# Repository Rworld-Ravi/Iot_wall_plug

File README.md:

# IoT wall plug standard

This is a circuit to control any 220v AC device under 4A plugged it.  

## Getting Started with another firmware  

To program the ESP8266 ESP-07 you need an USB <--> serial converter at 3,3v (5v will damage the ESP-07 IOs).  
You can use Arduino IDE to update own sketches.  
Or you can install another firmware in ESP-07 as Lua, uPython, ESPeasy...  
To install another firmware:
* Disconnect device from power  
* Shortcut jumper (IO0 and GND)  
* Connect your favorite USB-serial converter at RX,TX,GND pins  
* Apply power to device (Be careful with 220v AC)
* Upload your firmware with esptool.exe (windows) or another tool for OSX, Linux...  
* Disconnect the jumper (IO0 and GND)
* And restart device

## Built With

[EagleCAD](https://www.autodesk.com/products/eagle/overview)

## Authors

* **RadikalBytes** - *Alfredo Prado* - [@radikalbytes](https://twitter.com/radikalbytes)

## License
<br />This work is licensed under a <a rel="license" href="http://creativecommons.org/licenses/by-sa/3.0/">Creative Commons Attribution-ShareAlike 3.0 Unported License</a>.

## Acknowledgments

* To my brain for support me every hour ;)

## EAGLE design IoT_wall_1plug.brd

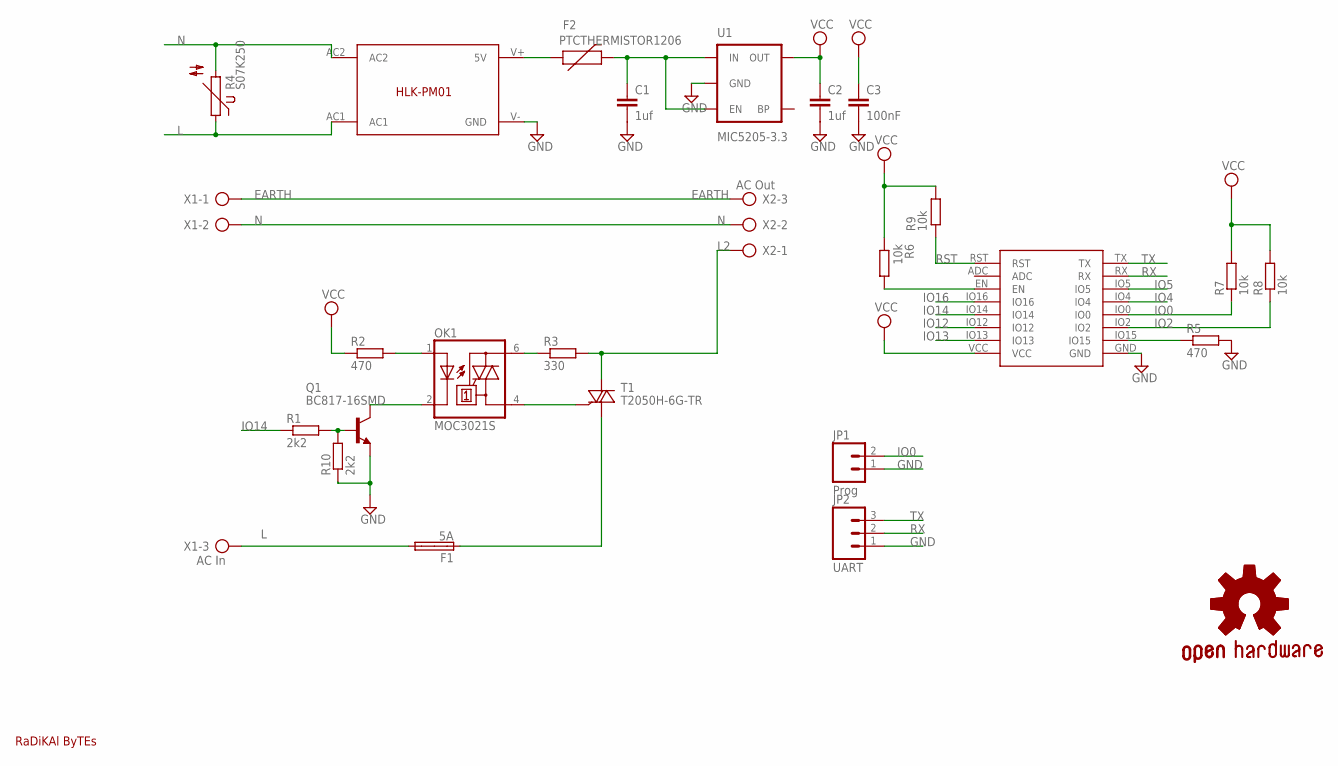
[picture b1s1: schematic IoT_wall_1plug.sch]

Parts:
C1, C2: 1uf; RCL_C0805K
C3: 100nF; RCL_C0805K
F1: 5A; SHK20Q
F2: PTCTHERMISTOR1206; SPARKFUN-POWERIC_PTC-1206
GOLD_ORB_SM1: OSHWLOGO_GOLD_ORB_MED; OSHW1
JP1: Prog; SPARKFUN-CONNECTORS_1X02
JP2: UART; SPARKFUN-CONNECTORS_1X03
OK1: MOC3021S; DIL6-SMD
Q1: BC817-16SMD; SOT23-BEC
R1, R10: 2k2; R0805
R2, R5: 470; R0805
R3: 330; R0805
R4: S07K250
R6, R7, R8, R9: 10k; R0805
T1: T2050H-6G-TR; D2PAK-3
U1: MIC5205-3.3; SPARKFUN-POWERIC_SOT23-5
U$1: HLK-PM01
U$2: DAVLIB_ESP8266
U$4: MI_LOGO1.5MM; MI_LOGO_PEQUEÑO
X1: AC In; AK500/3
X2: AC Out; AK500/3

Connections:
EARTH: X1.1, X2.3
GND: C1.2, C2.2, C3.2, JP1.1, JP2.1, Q1.E, R5.2, R10.1, U1.2 (GND), U$1.V- (GND), U$2.GND
IO0: JP1.2, R7.1, U$2.IO0
IO2: R8.1, U$2.IO2
IO4: U$2.IO4
IO5: U$2.IO5
IO12: U$2.IO12
IO13: U$2.IO13
IO14: R1.1, U$2.IO14
IO16: U$2.IO16
L: F1.2A, R4.1, U$1.AC1, X1.3
L2: R3.2, T1.4 (A2), X2.1
N: R4.2, U$1.AC2, X1.2, X2.2
unnamed: Q1.B, R1.2, R10.2
unnamed: OK1.1 (A), R2.2
unnamed: OK1.6 (A2), R3.1
unnamed: OK1.2 (C), Q1.C
unnamed: F1.1A, T1.1 (A1)
unnamed: F2.1, U$1.V+ (5V)
unnamed: OK1.4 (A1), T1.3 (G)
unnamed: C1.1, F2.2, U1.1 (IN), U1.3 (EN)
unnamed: R6.2, U$2.EN
unnamed: R5.1, U$2.IO15
RST: R9.1, U$2.RST
RX: JP2.2, U$2.RX
TX: JP2.3, U$2.TX
VCC: C2.1, C3.1, R2.1, R6.1, R7.2, R8.2, R9.2, U1.5 (OUT), U$2.VCC

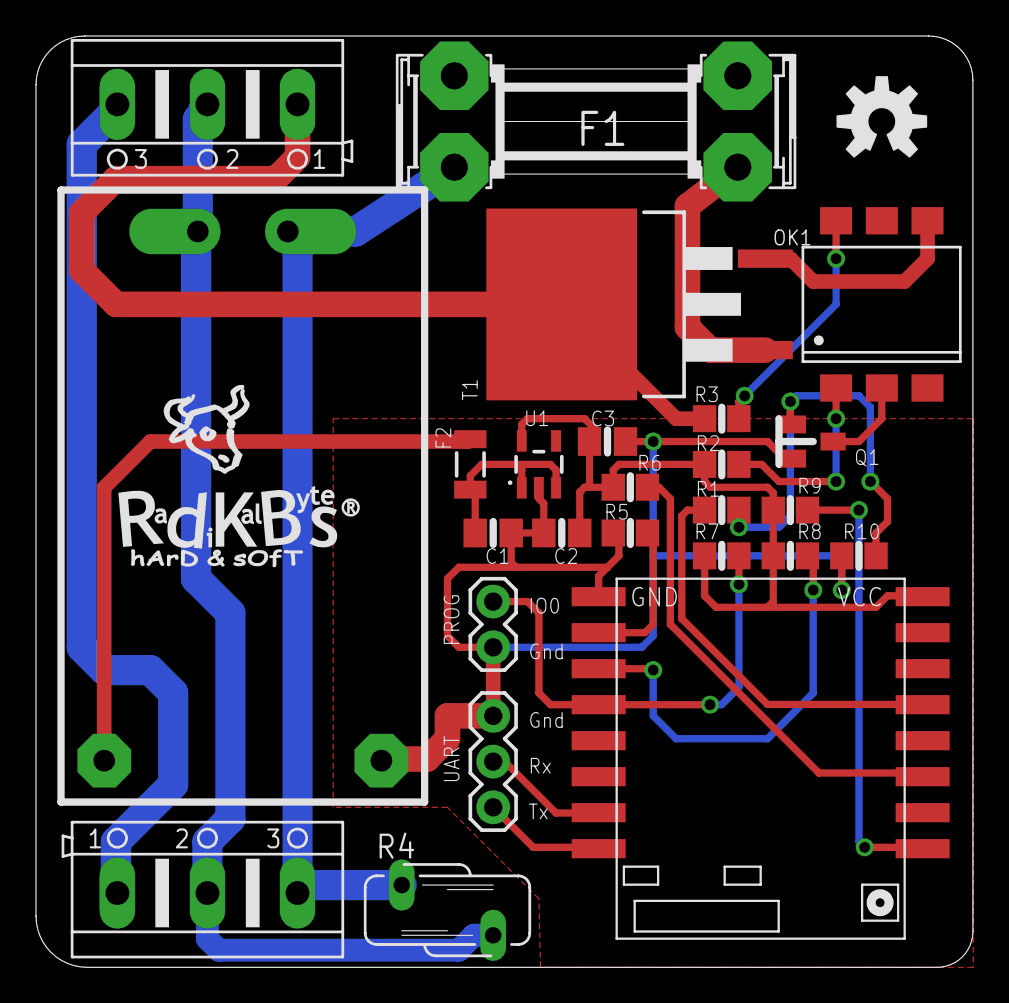
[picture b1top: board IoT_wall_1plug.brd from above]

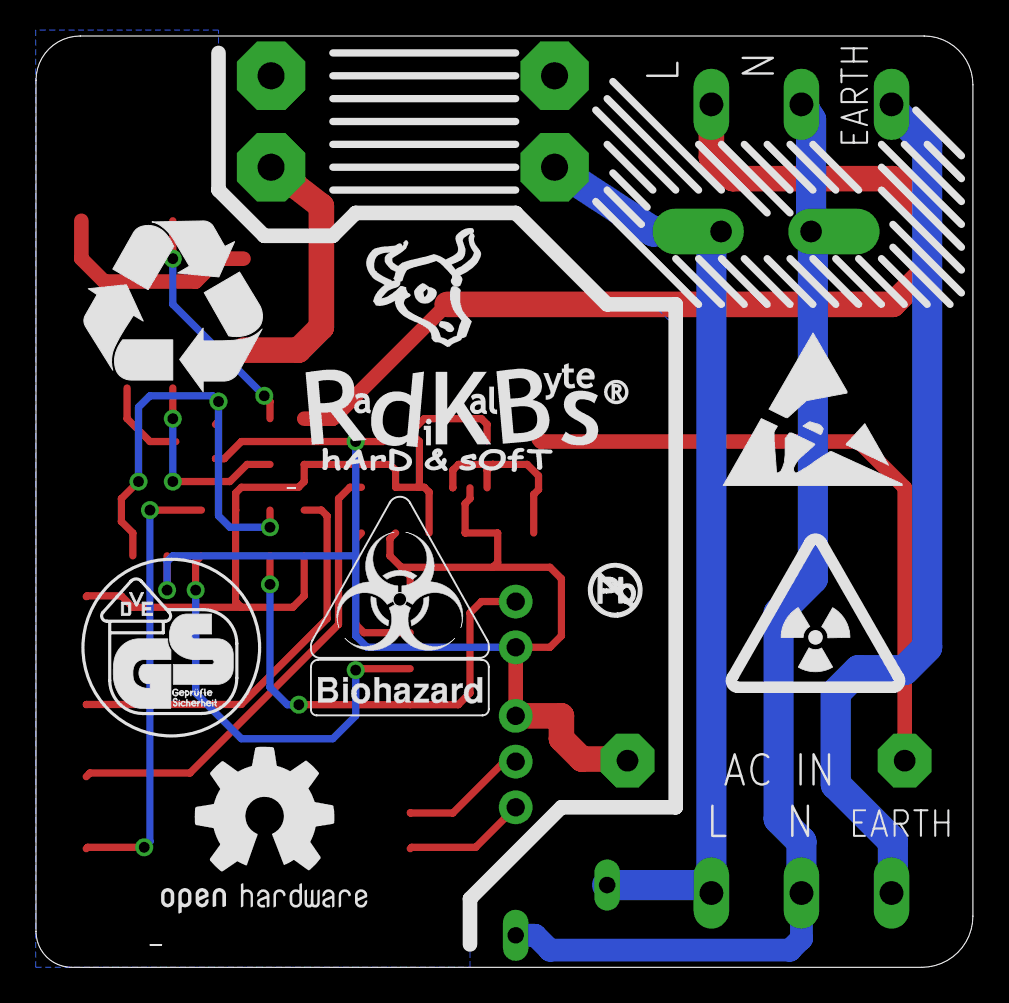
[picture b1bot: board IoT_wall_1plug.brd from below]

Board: 2 copper layers, 52.0 x 51.7 mm, 35 parts (8 on the bottom side), 22 nets.

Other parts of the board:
U$3: OSHW-LOGO-M
U$5: VDE-GS_10.00
U$6: RECYCLING_10.00
U$7: RADIOACTIVE_10.00
U$8: ESD_10.00
U$9: BIOHAZARD_10.00
U$10: NO_PB_LOGO_0.120
U$12: MI_LOGO_2MM

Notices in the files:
parts and their libraries:
SparkFun-Aesthetics: Licensing: Creative Commons ShareAlike 4.0 International - https://creativecommons.org/licenses/by-sa/4.0
